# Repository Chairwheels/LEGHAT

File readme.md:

# Raspberry Pi 5 Battery Power HAT

This project was done in KiCad as I found it easier to work in and had more support throughout the industry as it is second in use only to Altium designer for PCB design tools.

## Project goal

Design a four-layer Raspberry Pi 5 HAT that powers the Pi through its 40-pin header from a **33.3–37.8 V battery** instead of its USB-C power input. The board uses an isolated DC/DC converter, input protection, and a MOSFET-based backfeed protection. It also breaks out SPI for two encoders and a load-cell data-acquisition (DAQ) board, and includes a pushbutton and two LEDs for either USB or PI Shutdown.

## PCB outline and references

- The PCB outline and Raspberry Pi HAT+ mechanical template are based on [MisterHW/RPi5-HATplus](https://github.com/MisterHW/RPi5-HATplus). The power circuitry and peripheral interface in this project are project-specific. Check the original repository and its [CERN-OHL-S v2 licence](https://ohwr.org/cern_ohl_s_v2.txt) when redistributing derived design files.
- The 8-pin SPI connector concept was informed by the University of Michigan Neurobionics Lab's [Open-Source Leg interface board](https://opensourceleg.org/electronics/interface-board/), which documents an 8-pin Molex Pico-Clasp SPI-1 port with three chip selects. The load-cell DAQ concept references the [Open-Source Leg DAQ board](https://opensourceleg.org/electronics/daq/).
- The OSL interface board references the **MOLEX Pico-Clasp**. The **Micro-Clasp** was used here as the Pico-Clasp is not available through JLCPCB

## Parts and PCB designations

The designators below follow the current schematic and parts list. 

| PCB designation | Part / selection | Function |
| --- | --- | --- |
| J1 | Raspberry Pi 40-pin header; Samtec SSW-120-01-F-D | Connects power, ground, SPI, and control signals to the Pi GPIO header. |
| J2 | AMASS XT30UPB-F | Battery input connector. |
| F1 | Bel Fuse 0680L3000-05, 3 A  | Input overcurrent protection |
| D1 | Vishay SS5P10-M3/86A | Series Schottky diode for input reverse polarity protection. |
| D2 | Vishay SMCJ43A-E3/57T | TVS diode for input transient suppression. |
| C1 | Samsung CL31B105KCHNNNE, 1 µF | High frequency bypass on the battery/converter input. |
| C2 | Panasonic EEEFK2A221AM, 220 µF  | Battery side bulk input capaciter. |
| PS1 | TRACO Power THN 30-4811WI | Isolated DC/DC converter from battery voltage to the low-voltage rail. |
| R1 | Panasonic ERJPB3B4992V, 49.9 kΩ  | Fixed resistor in the converter trim network. |
| RV1 | Bourns 3224W-1-204E, 200 kΩ  | Adjustable resistor in the converter trim network. |
| C3 | Samsung CL32B226KAJNNNE, 22 µF  | Converter output capacitance before the backfeed protection stage. |
| Q2 | Texas Instruments CSD18540Q5B | MOSFET in the backfeed protection stage. |
| U4 | Analog Devices LTC4373IDD#PBF | Ideal diode controller for the MOSFET backfeed protection stage. |
| C4 | TDK C1005X7R1E104KT000F, 100 nF | Local bypass capacitor for U4. |
| C5 | Panasonic 16SVPC100M, 100 µF | Bulk capacitance on the protected `HAT_5V0` output. |
| J3 | Molex 55932-0810, 8-circuit MicroClasp header | Peripheral connector for 3.3 V, ground, SPI clock/data, and chip-select signals. |
| C7 | Vishay VJ0603Y104JXQCW1BC, 100 nF | High frequency decoupling for the peripheral 3.3 V supply near J3. |
| C8 | Samsung CL10B105KP8NNNC, 1 µF | Local decoupling for the peripheral 3.3 V supply near J3. |
| SW1 | Omron B3SL-1022P | Pushbutton for the planned shutdown interface. |
| D3 | Lite-On LTST-C191KGKT, green LED | Green status indicator (`GREEN_LED`). |
| D4 | Lite-On LTST-C191KRKT, red LED | Red status indicator (`RED_LED`). |
| R2, R3 | Yageo AC0603FR-07470RL, 470 Ω | Current limiting resistors for the green and red LEDs. |

## Connections

### Power path

1. Battery positive enters at **J2 pin 2**, then passes through **F1** and **D1** to the input of **PS1**.
2. Battery negative enters at **J2 pin 1** and is labelled `Bat_Neg`. **D2**, **C1**, and **C2** are connected across the battery side input as shown in the schematic.
3. **PS1** provides isolated low-voltage output. The input side and output side are seperate circuits and have seperate ground planes on the inner copper layers of the PCB.
4. **R1/RV1** form the converter trim network. 
5. **Q2/U4** provide the planned backfeed-protection stage in the form of a MOSFET/Ideal Diode configuration. The protected rail is labelled `HAT_5V0` and feeds the Pi header at J1 pins 2 and 4.

### J3 — 8-pin encoder / DAQ SPI connector

This table records the signal order shown in the current schematic. It is the pinout for the molex connector. The OSL pinouts were used as reference.

| J3 pin | Net | Purpose |
| ---: | --- | --- |
| 1 | `HAT_3.3V` | 3.3 V peripheral supply |
| 2 | `SPI1_CSn2` | SPI1 chip-select net 2 |
| 3 | `SPI1_CSn1` | SPI1 chip-select net 1 |
| 4 | `SPI1_CSn0` | SPI1 chip-select net 0 |
| 5 | `SPI1_SCLK` | SPI clock |
| 6 | `SPI1_MISO` | Pi-to-peripheral data return (peripheral output) |
| 7 | `SPI1_MOSI` | Pi-to-peripheral data (Pi output) |
| 8 | `HAT_GND` | Pi-side ground reference |

The two encoders and the DAQ share `SPI1_SCLK`, `SPI1_MOSI`, and `SPI1_MISO`. Each device uses its own chip-select. The load cell connects to the DAQ, then to the Pi.

### J1 — Raspberry Pi 40-pin header Pinouts

The Pi header assignments below use the standard Raspberry Pi 40-pin header pinout and the SPI1 mapping.

| J1 pin | Intended net / signal | Purpose |
| ---: | --- | --- |
| 1, 17 | `HAT_3.3V` | 3.3 V rail for peripheral logic |
| 2, 4 | `HAT_5V0` | Protected 5 V supply to the Pi |
| 6, 9, 14, 20, 25, 30, 34, 39 | `HAT_GND` | Pi-side ground |
| 11 | `SPI1_CSn1` | SPI1 chip select 1 / GPIO17 |
| 12 | `SPI1_CSn0` | SPI1 chip select 0 / GPIO18 |
| 18 | `GREEN_LED` | Green LED control / GPIO24 |
| 22 | `RED_LED` | Red LED control / GPIO25 |
| 35 | `SPI1_MISO` | SPI1 MISO / GPIO19 |
| 36 | `SPI1_CSn2` | SPI1 chip select 2 / GPIO16 |
| 37 | `PWR_Switch` | Shutdown button signal / GPIO26 |
| 38 | `SPI1_MOSI` | SPI1 MOSI / GPIO20 |
| 40 | `SPI1_SCLK` | SPI1 clock / GPIO21 |

The SPI1 mapping follows the [Raspberry Pi documentation](https://www.raspberrypi.com/documentation/computers/raspberry-pi.html): CE0 on physical pin 12, CE1 on pin 11, CE2 on pin 36, MISO on pin 35, MOSI on pin 38, and SCLK on pin 40. The `SPI1_CSn0`, `SPI1_CSn1`, and `SPI1_CSn2` nets on J1 should connect to the corresponding chip-select signals on J3. 

## Test Points and PCB Measurement Locations

The PCB includes six numbered test points to simplify power testing and troubleshooting. Ground measurement references are provided by vias connected to the appropriate ground planes.

### Test Point Locations

| Test Point | Net | PCB Location | Purpose |
| --- | --- | --- | --- |
| TP1 | `J2-Pin_2` | At J2's battery connection before F1 | Measures the battery voltage before the fuse and input protection. |
| TP2 | `D1-K (On D1)` | Between F1 and D1 | Measures if the battery voltage passes through the input fuse. |
| TP3 | `D1-K (On C1` | After D1, near the positive input pin of PS1 | Measures the voltage reaching the TRACO DC/DC converter after input protection. |
| TP4 | `PS1-+VOUT` | At the converter output, near C3 and the converter-side terminal of Q2 | Measures the converter output before the MOSFET backfeed protection. |
| TP5 | `HAT_5V0` | On the protected side of Q2, near C5 and J1 | Measures the final 5 V supply delivered to the Raspberry Pi. |
| TP6 | `HAT_3.3V` | Near J3 pin 1, on the peripheral 3.3 V supply | Makes sure the MOLEX connector receives its 3.3 V supply from the Raspberry Pi. |

### Ground Reference Vias

Two separate ground reference vias are used for measurements:

- **`BAT_NEG` via:** Located between TP1 and D1. Use this as the reference when measuring TP1, TP2, and TP3.
- **`HAT_GND` via:** Located between TP4 and TP5 near HAT_5V0 net. Use this as the reference when measuring TP4, TP5, and TP6.

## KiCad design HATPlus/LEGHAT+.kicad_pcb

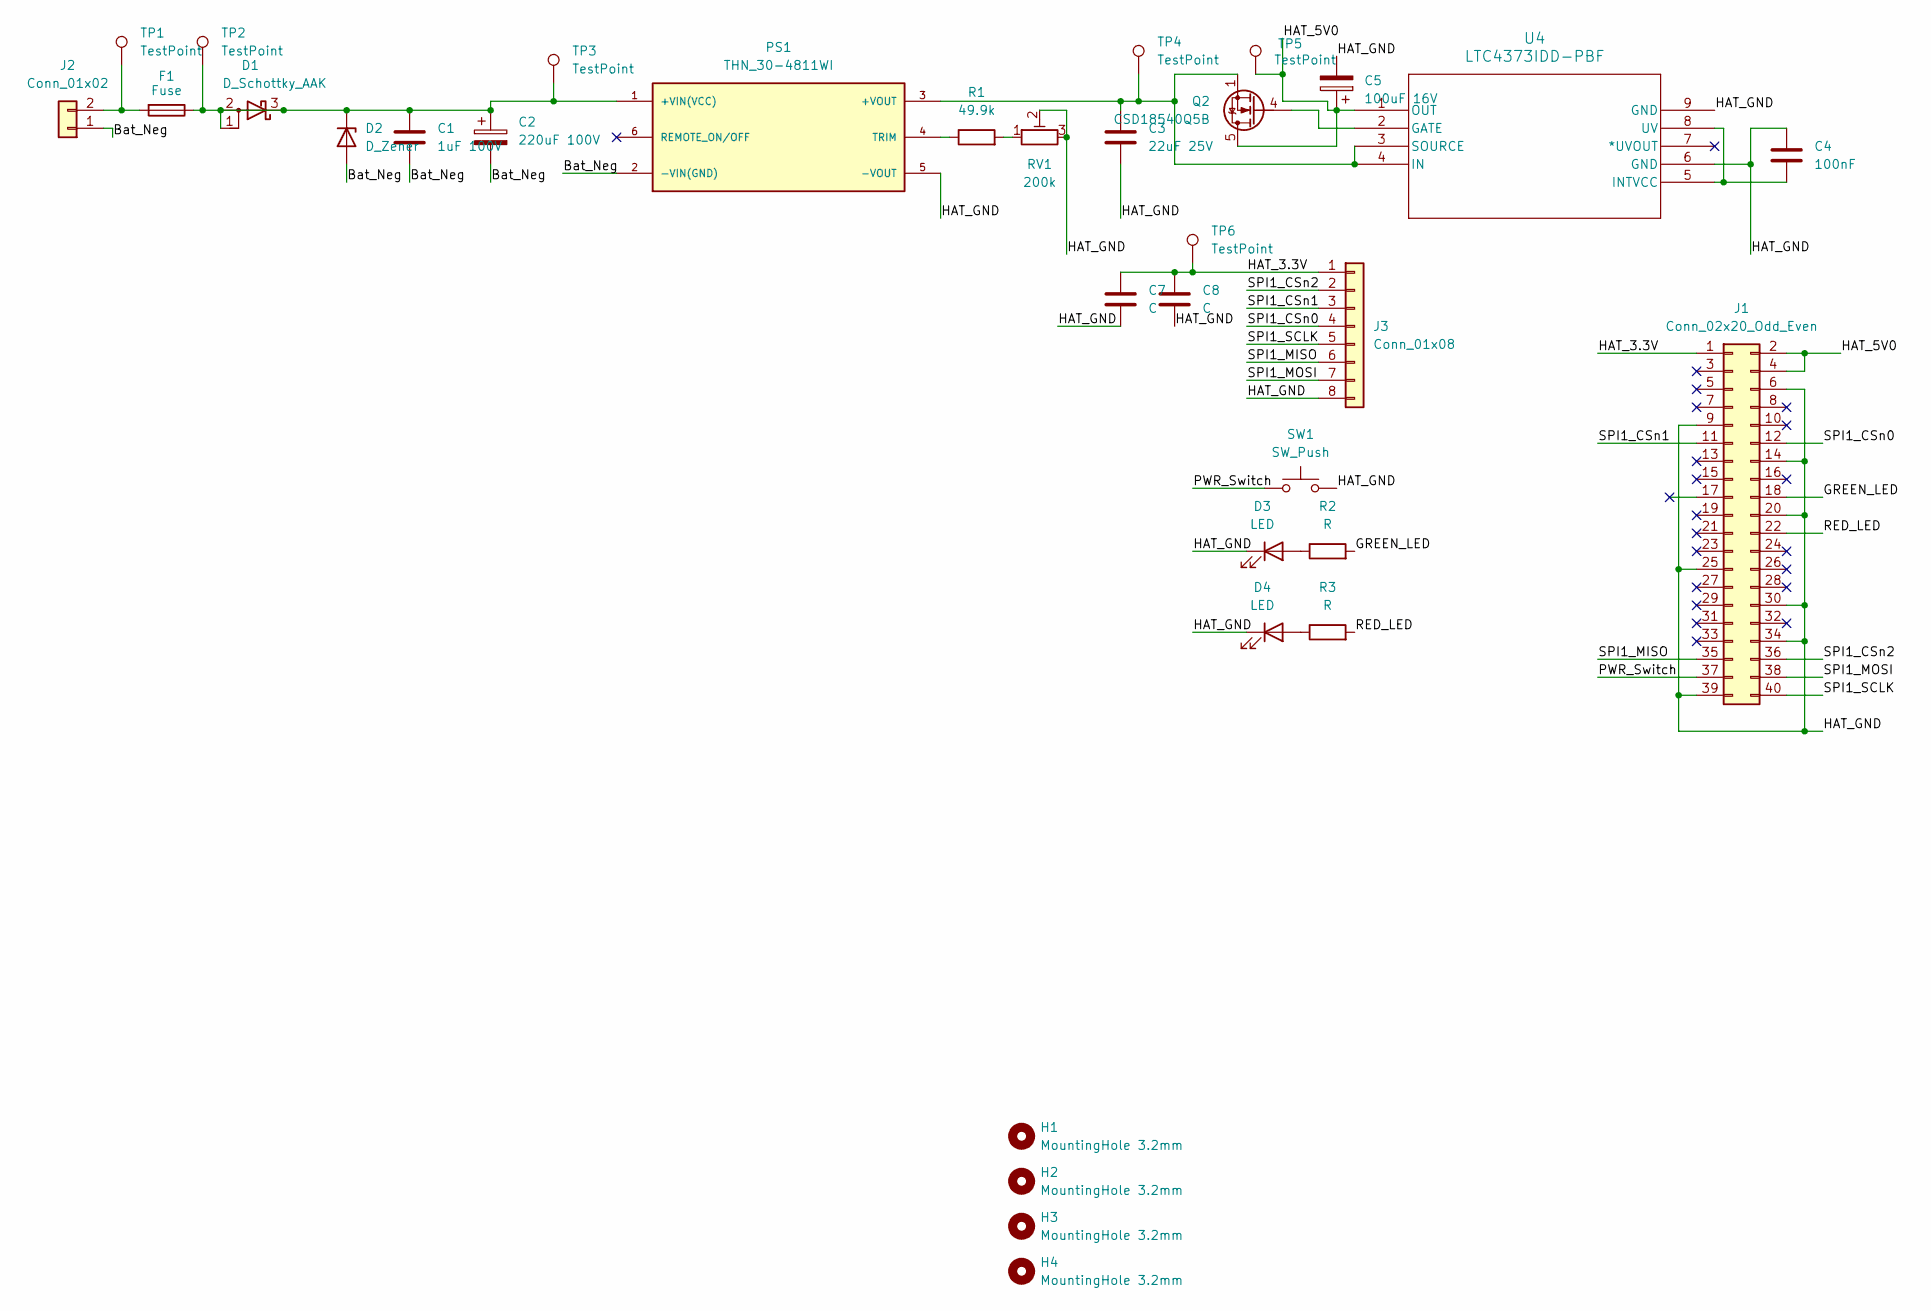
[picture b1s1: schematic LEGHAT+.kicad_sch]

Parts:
C1: 1uF 100V; C_1206_3216Metric
C2: 220uF 100V; CAP_EEEFK2A221AM
C3: 22uF 25V; C_1210_3225Metric
C4: 100nF; CP_Elec_6.3x5.8
C5: 100uF 16V; C_0402_1005Metric
C7, C8: C; C_0603_1608Metric
D1: D_Schottky_AAK; TO-277A
D2: D_Zener; D_SMC
D3, D4: LED; LED_0603_1608Metric
F1: Fuse; FUSC6125X279N
H1, H2, H3, H4: MountingHole 3.2mm; MountingHole_3.2mm_M3_DIN965
J1: Conn_02x20_Odd_Even; PinSocket_2x20_P2.54mm_Vertical
J2: Conn_01x02; AMASS_XT30UPB-F_1x02_P5.0mm_Vertical
J3: Conn_01x08; Molex_MicroClasp_55932-0810_1x08_P2.00mm_Vertical
PS1: THN_30-4811WI; Converter_DCDC_TRACO_THN30-xxxx_THT; PARTREV March 16, 2021; DigiKey_Part_Number 1951-1711-ND
Q2: CSD18540Q5B; DNK0008A
R1: 49.9k; R_0603_1608Metric
R2, R3: R; R_0603_1608Metric
RV1: 200k; Potentiometer_Bourns_3224W_Vertical
SW1: SW_Push; SW_SPST_B3SL-1022P
TP1, TP2, TP3, TP4, TP5, TP6: TestPoint; TestPoint_Pad_D1.0mm
U4: LTC4373IDD-PBF; DFN8_DD_05-08-1698_ADI

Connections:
/Bat_Neg: C1.2, C2.2, D2.2 (A), J2.1, PS1.2 (-VIN(GND))
/GREEN_LED: J1.18, R2.2
/HAT_3.3V: C7.1, C8.1, J1.1, J3.1, TP6.1 (1_1)
/HAT_5V0: C5.1, J1.2, J1.4, Q2.5 (D), TP5.1 (1_1), U4.1 (OUT)
/HAT_GND: C3.2, C4.1, C5.2, C7.2, C8.2, D3.1 (K), D4.1 (K), J1.6, J1.9, J1.14, J1.20, J1.25, J1.30, J1.34, J1.39, J3.8, PS1.5 (-VOUT), RV1.2, RV1.3, SW1.2, U4.6 (GND), U4.9 (GND)
/PWR_Switch: J1.37, SW1.1
/RED_LED: J1.22, R3.2
/SPI1_CSn0: J1.12, J3.4
/SPI1_CSn1: J1.11, J3.3
/SPI1_CSn2: J1.36, J3.2
/SPI1_MISO: J1.35, J3.6
/SPI1_MOSI: J1.38, J3.7
/SPI1_SCLK: J1.40, J3.5
unnamed: C1.1, C2.1, D1.1 (A), D1.2 (A), D1.3 (K), D2.1 (K), F1.1, PS1.1 (+VIN(VCC)), TP2.1 (1_1), TP3.1 (1_1)
unnamed: D3.2 (A), R2.1
unnamed: D4.2 (A), R3.1
unnamed: F1.2, J2.2, TP1.1 (1_1)
unnamed: C3.1, PS1.3 (+VOUT), Q2.1 (S), Q2.2 (S), Q2.3 (S), TP4.1 (1_1), U4.3 (SOURCE), U4.4 (IN)
unnamed: PS1.4 (TRIM), R1.1
unnamed: Q2.4 (G), U4.2 (GATE)
unnamed: R1.2, RV1.1
unnamed: C4.2, U4.5 (INTVCC), U4.8 (UV)

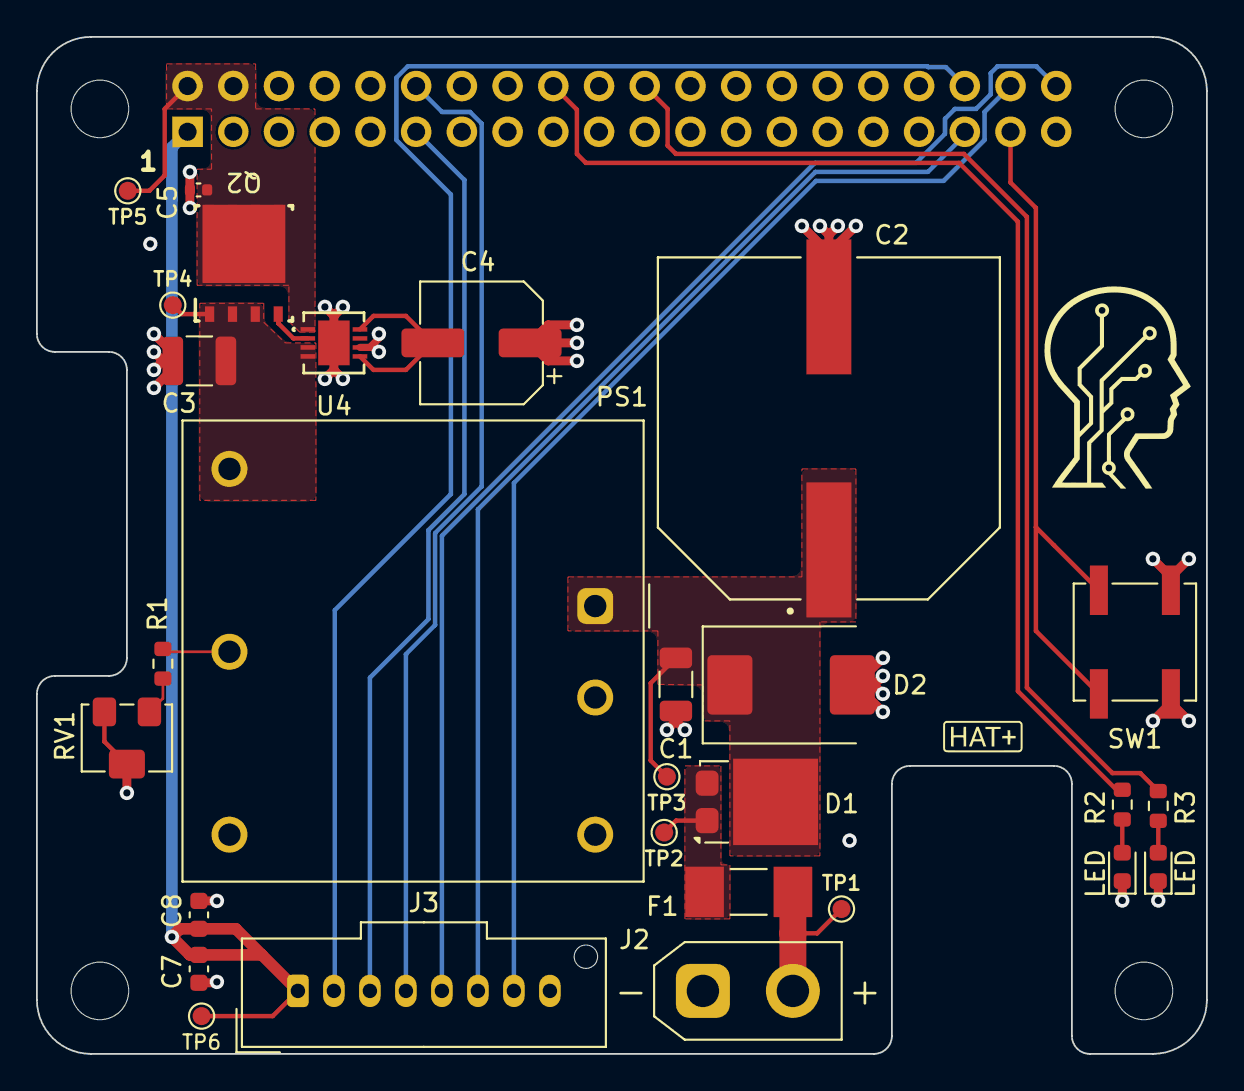
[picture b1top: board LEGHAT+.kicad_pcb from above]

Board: 4 copper layers, 65.0 x 56.5 mm, 33 parts (1 on the bottom side), 22 nets.

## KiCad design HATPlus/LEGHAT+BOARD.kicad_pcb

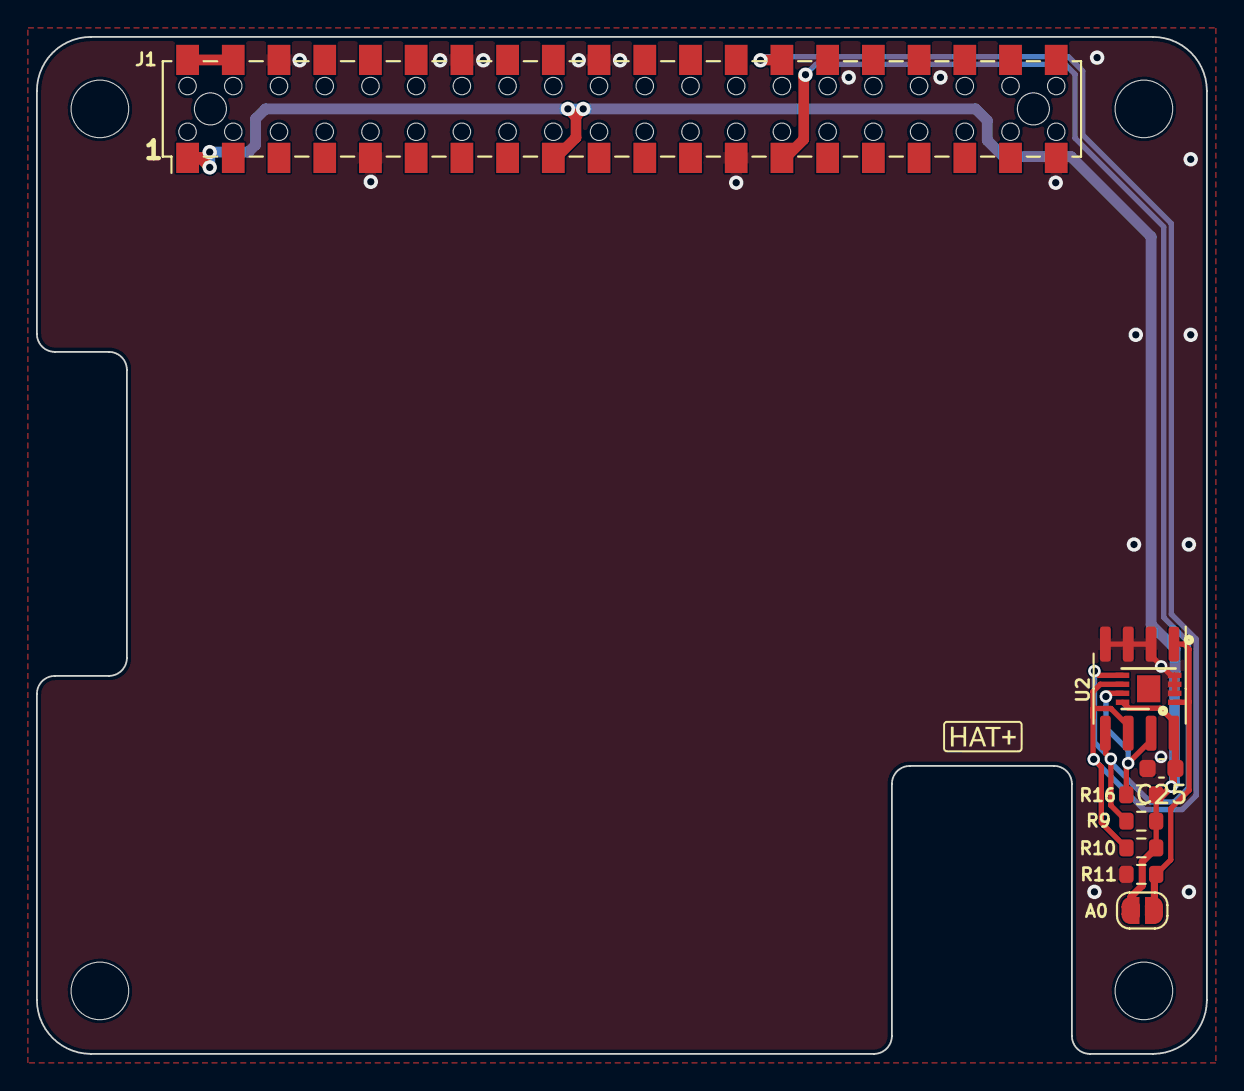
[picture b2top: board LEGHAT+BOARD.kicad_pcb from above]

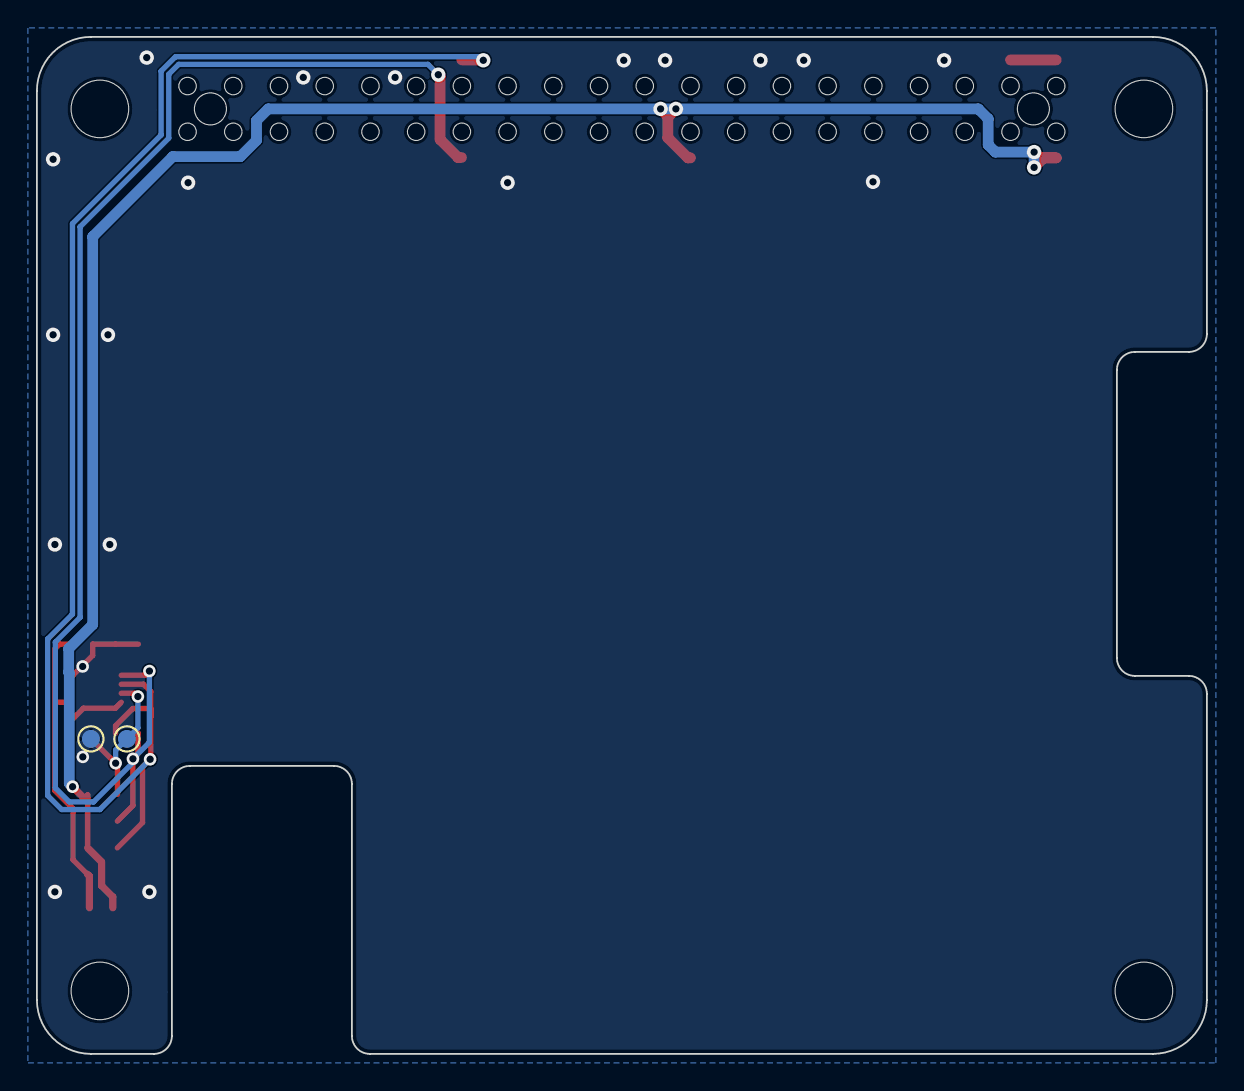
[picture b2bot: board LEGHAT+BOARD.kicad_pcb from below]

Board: 4 copper layers, 65.0 x 56.5 mm, 15 parts (2 on the bottom side), 7 nets.

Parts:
A0: SolderJumper_2_Open; SolderJumper-2_P1.3mm_Open_RoundedPad1.0x1.5mm
C25: 100nF; C_0603_1608Metric
GND1: TestPoint_Alt; TestPoint_Pad_D1.0mm
H1, H2, H3, H4: MountingHole 3.2mm; MountingHole_3.2mm_M3_DIN965
J1: Conn_02x20_Odd_Even; Samtec_HLE-120-02-xxx-DV-BE-A_2x20_P2.54mm_Horizontal_Rever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
R9, R10, R11, R16: 3.9k; R_0603_1608Metric
U1: AT24CS64-SSHM; SOIC-8_3.9x4.9mm_P1.27mm
U2: AT24CS64-MAHM; DFN-8-1EP_3x2mm_P0.5mm_EP1.3x1.5mm
WP1: TestPoint_Alt; TestPoint_Pad_D1.0mm

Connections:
/HAT+/HAT_3V3: A0.2 (B), C25.1, J1.1, J1.17, R9.2, R10.2, R16.2, U1.8 (VCC), U2.8 (VCC)
/HAT+/HAT_5V0: J1.2, J1.4
/HAT+/HAT_SCL0: J1.28, R10.1, U1.6 (SCL), U2.6 (SCL)
/HAT+/HAT_SDA0: J1.27, R9.1, U1.5 (SDA), U2.5 (SDA)
GND: C25.2, GND1.1, J1.6, J1.9, J1.14, J1.20, J1.25, J1.30, J1.34, J1.39, R11.1, U1.2 (A1), U1.3 (A2), U1.4 (GND), U2.2 (A1), U2.3 (A2), U2.4 (GND)
unnamed: A0.1 (A), R11.2, U1.1 (A0), U2.1 (A0)
unnamed: R16.1, U1.7 (WP), U2.7 (WP), WP1.1

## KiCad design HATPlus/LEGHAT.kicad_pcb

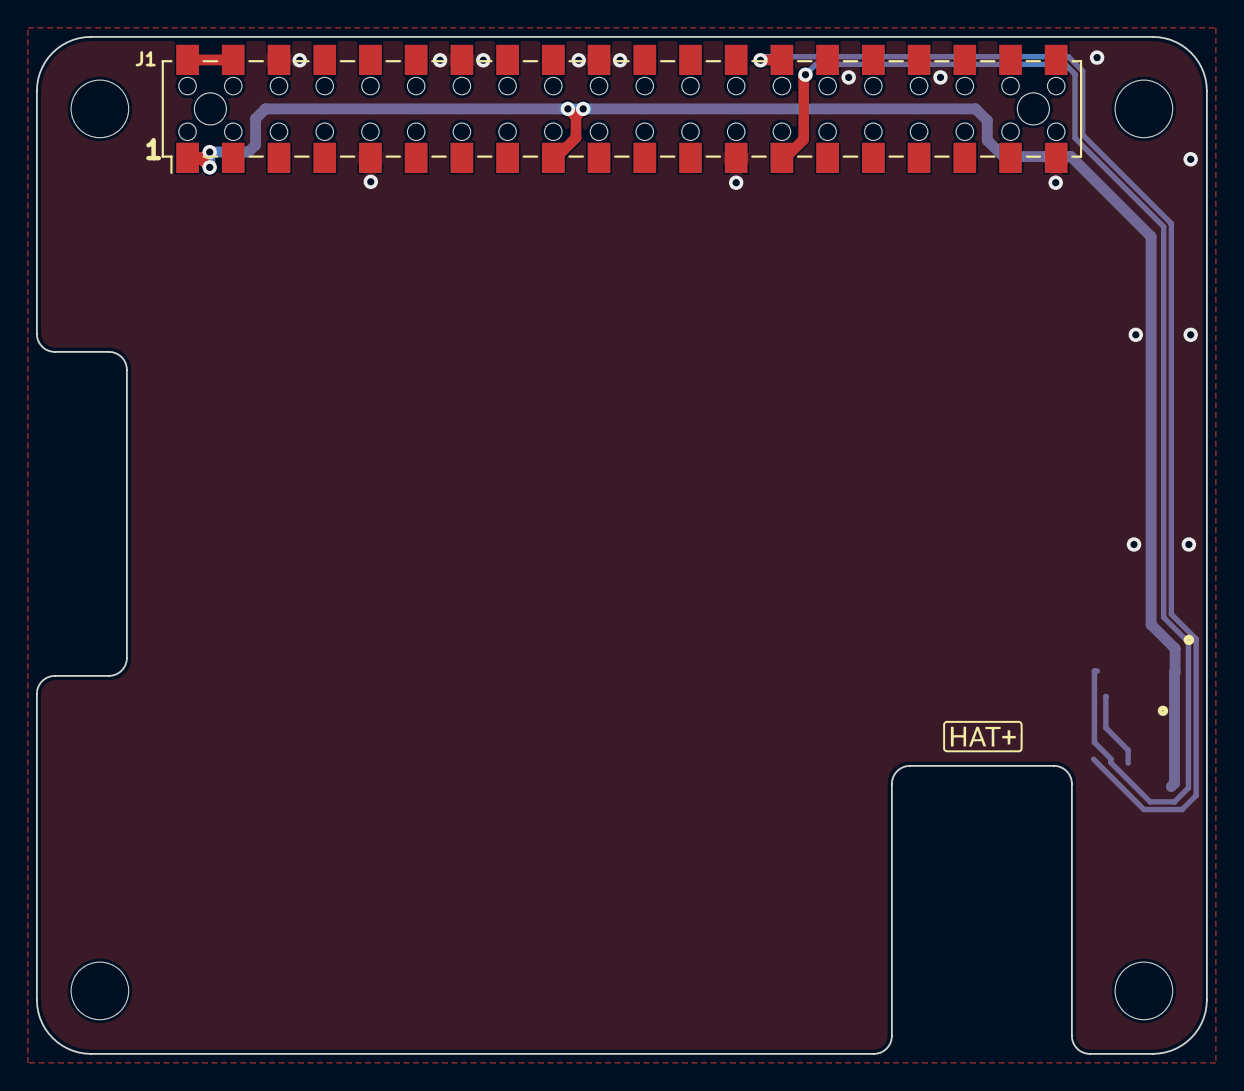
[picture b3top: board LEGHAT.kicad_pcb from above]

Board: 4 copper layers, 65.0 x 56.5 mm, 5 parts (0 on the bottom side), 3 nets.

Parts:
H1, H2, H3, H4: MountingHole 3.2mm; MountingHole_3.2mm_M3_DIN965
J1: Conn_02x20_Odd_Even; Samtec_HLE-120-02-xxx-DV-BE-A_2x20_P2.54mm_Horizontal_Rever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

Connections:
/HAT+/HAT_3V3: J1.1, J1.17
/HAT+/HAT_5V0: J1.2, J1.4
GND: J1.6, J1.9, J1.14, J1.20, J1.25, J1.30, J1.34, J1.39
